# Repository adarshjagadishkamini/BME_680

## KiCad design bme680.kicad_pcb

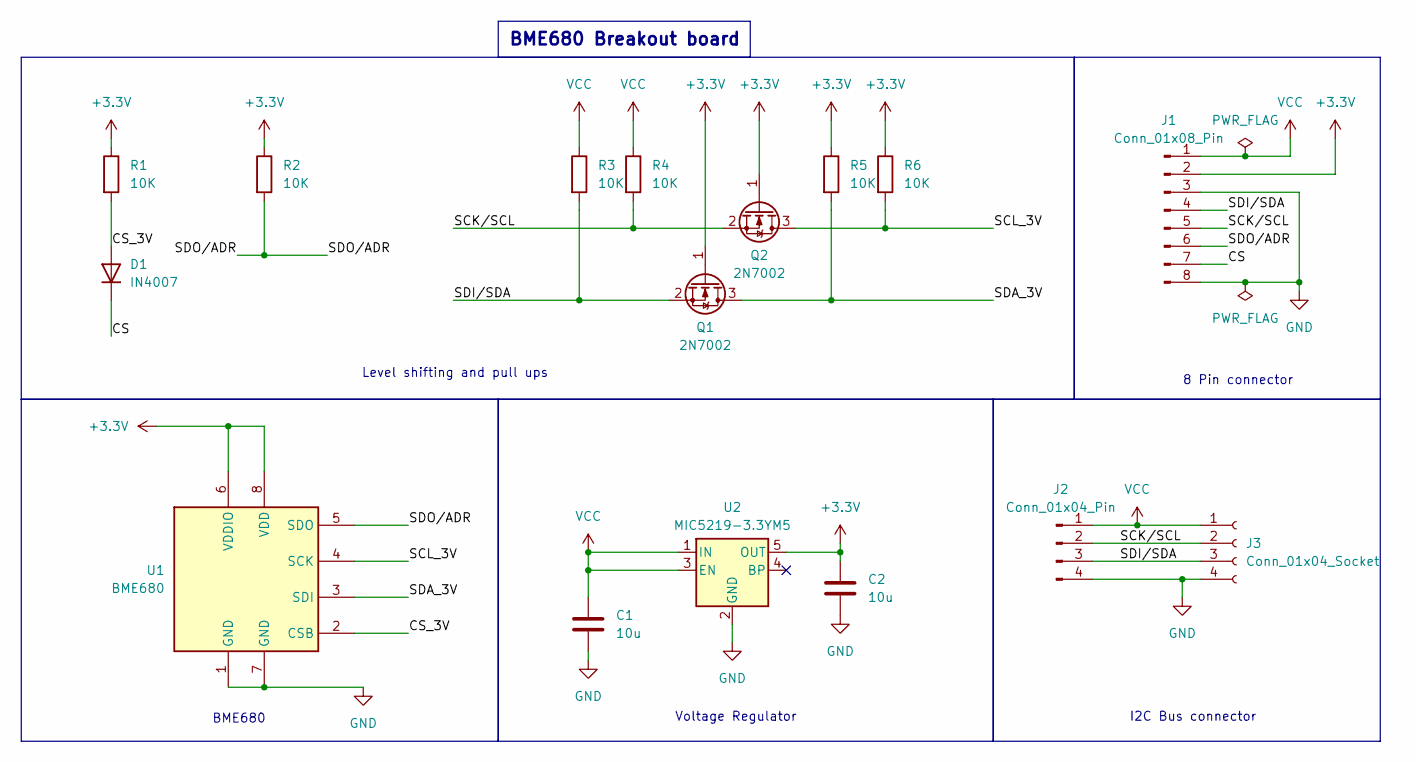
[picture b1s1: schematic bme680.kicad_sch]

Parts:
C1, C2: 10u; C_1210_3225Metric
D1: IN4007; D_1206_3216Metric
J1: Conn_01x08_Pin; JST_PH_S8B-PH-K_1x08_P2.00mm_Horizontal
J2: Conn_01x04_Pin; PinSocket_1x04_P2.54mm_Horizontal
J3: Conn_01x04_Socket; PinSocket_1x04_P2.54mm_Horizontal
Q1, Q2: 2N7002; SOT-23
R1, R2, R3, R4, R5, R6: 10K; R_1206_3216Metric
U1: BME680; Bosch_LGA-8_3x3mm_P0.8mm_ClockwisePinNumbering
U2: MIC5219-3.3YM5; SOT-23-5

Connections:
+3.3V: C2.1, J1.2, Q1.1 (G), Q2.1 (G), R1.1, R2.1, R5.1, R6.1, U1.6 (VDDIO), U1.8 (VDD), U2.5 (OUT)
/CS: D1.1 (K), J1.7
/CS_3V: D1.2 (A), R1.2, U1.2 (CSB)
/SCK/SCL: J1.5, J2.2, J3.2, Q2.2 (S), R4.2
/SCL_3V: Q2.3 (D), R6.2, U1.4 (SCK)
/SDA_3V: Q1.3 (D), R5.2, U1.3 (SDI)
/SDI/SDA: J1.4, J2.3, J3.3, Q1.2 (S), R3.2
/SDO/ADR: J1.6, R2.2, U1.5 (SDO)
GND: C1.2, C2.2, J1.3, J1.8, J2.4, J3.4, U1.1 (GND), U1.7 (GND), U2.2 (GND)
VCC: C1.1, J1.1, J2.1, J3.1, R3.1, R4.1, U2.1 (IN), U2.3 (EN)

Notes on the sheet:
BME680 Breakout board
BME680
I2C Bus connector
Level shifting and pull ups
Voltage Regulator
8 Pin connector

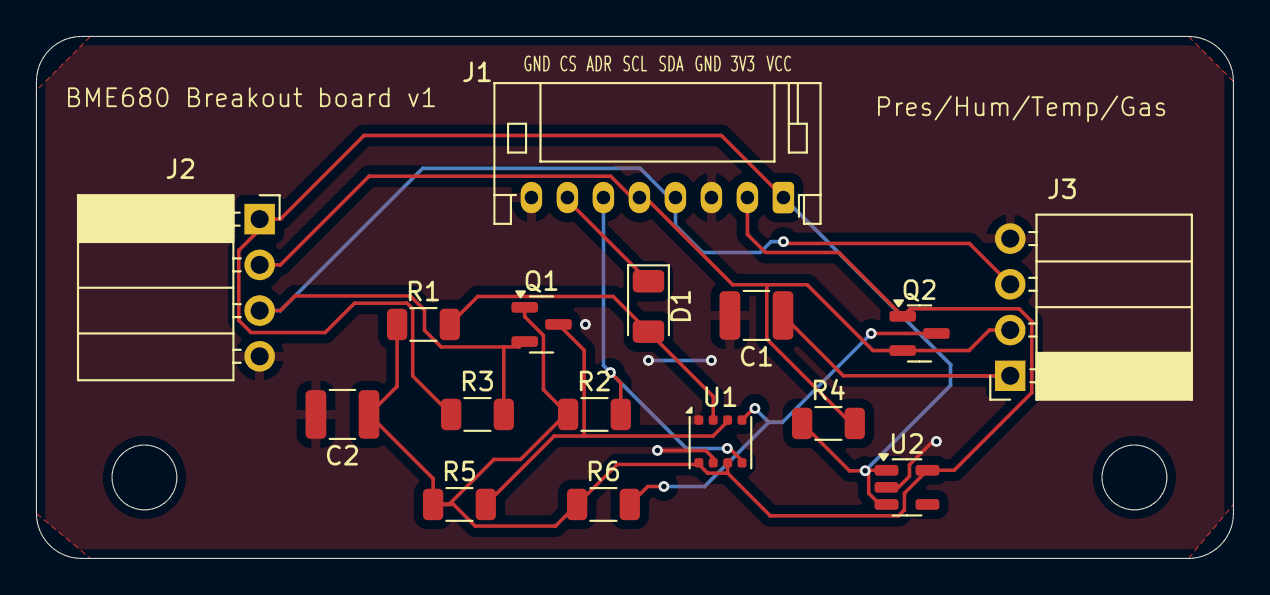
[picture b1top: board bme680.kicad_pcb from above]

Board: 2 copper layers, 66.5 x 29.0 mm, 16 parts (0 on the bottom side), 10 nets.
